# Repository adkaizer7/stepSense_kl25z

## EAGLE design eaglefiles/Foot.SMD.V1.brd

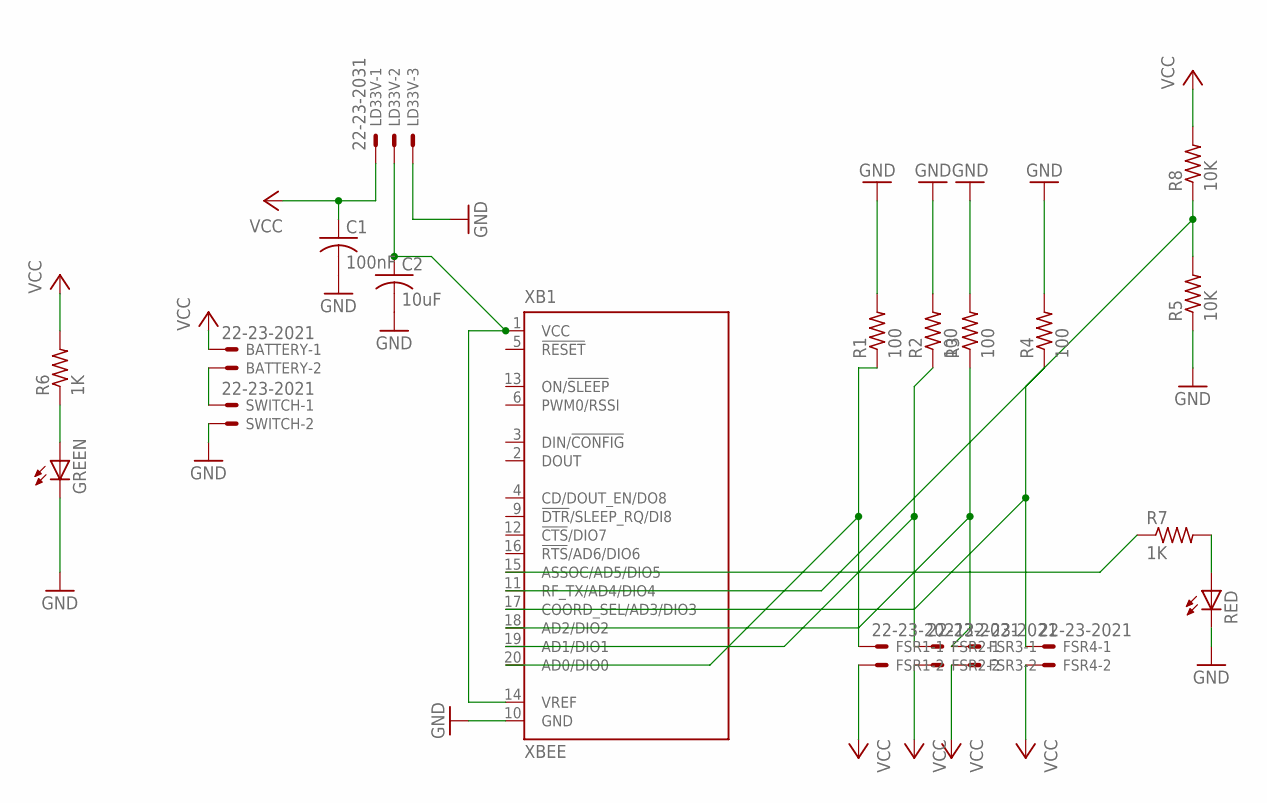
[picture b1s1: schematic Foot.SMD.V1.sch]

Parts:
BATTERY: 22-23-2021
C1: 100nF; C1206
C2: 10uF; C1206
FSR1, FSR2, FSR3, FSR4: 22-23-2021
GREEN: LED_E; LED_1206
LD33V: 22-23-2031
R1, R2, R3, R4: 100; M1206
R5, R8: 10K; M1206
R6, R7: 1K; M1206
RED: LED_E; LED_1206
SWITCH: 22-23-2021
XB1: XBEE

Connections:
GND: C1.2, C2.2, GREEN.C, LD33V.3, R1.2, R2.2, R3.2, R4.2, R5.1, RED.C, SWITCH.2, XB1.10 (GND)
unnamed: R5.2, R8.1, XB1.11 (RF_TX/AD4/DIO4)
unnamed: GREEN.A, R6.1
unnamed: R7.2, RED.A
unnamed: BATTERY.2, SWITCH.1
unnamed: C2.1, LD33V.2, XB1.1 (VCC), XB1.14 (VREF)
unnamed: FSR1.1, R1.1, XB1.20 (AD0/DIO0)
unnamed: FSR2.1, R2.1, XB1.19 (AD1/DIO1)
unnamed: FSR3.1, R3.1, XB1.18 (AD2/DIO2)
unnamed: FSR4.1, R4.1, XB1.17 (COORD_SEL/AD3/DIO3)
unnamed: R7.1, XB1.15 (ASSOC/AD5/DIO5)
VCC: BATTERY.1, C1.1, FSR1.2, FSR2.2, FSR3.2, FSR4.2, LD33V.1, R6.2, R8.2

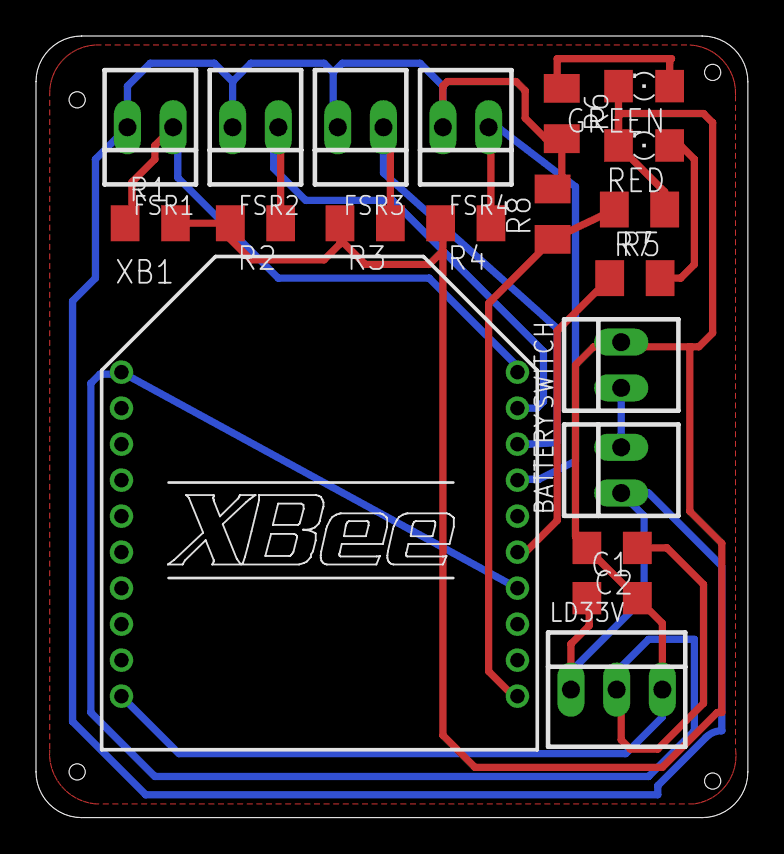
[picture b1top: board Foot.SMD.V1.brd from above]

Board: 2 copper layers, 39.5 x 43.4 mm, 20 parts (0 on the bottom side), 12 nets.

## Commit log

2014-12-01 kl25z_1 [x] With uart support to read data from xbee [x] Sending data one byte at a time to nrf51822.
2014-12-01 kl25z_2
    [x]Able to read most values.
    [x]These values are being broadcasted using BLE
2014-12-01 kl25z_3
    [x] One entire loop works
2015-05-26 Latest code i
2015-05-26 Adding the eagle files
2015-05-26 Latest code
